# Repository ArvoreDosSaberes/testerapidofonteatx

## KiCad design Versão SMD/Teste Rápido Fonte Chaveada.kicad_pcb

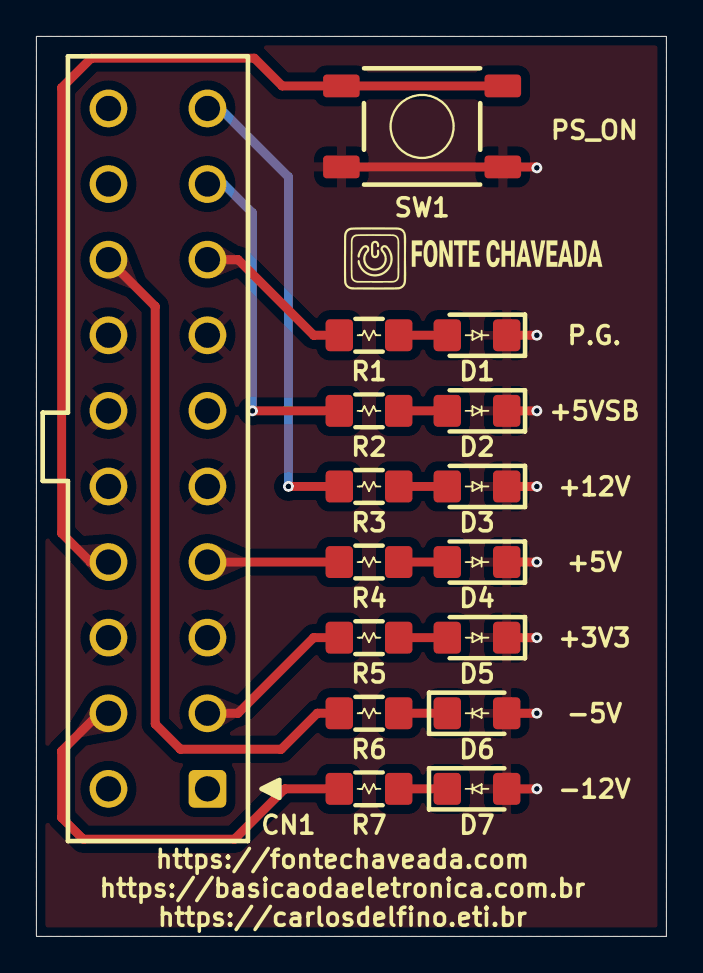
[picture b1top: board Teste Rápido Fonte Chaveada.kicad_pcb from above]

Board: 2 copper layers, 35.0 x 50.0 mm, 16 parts (0 on the bottom side), 16 nets.

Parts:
CN1: W4505-20PDRDTXR
D1, D2, D3, D4, D5, D6, D7: LED; LED_1206_HandSolder
R1, R4, R6: 470R; RES_1206_HandSolder
R2: 680R; RES_1206_HandSolder
R3: 1K8R; RES_1206_HandSolder
R5: 100R; RES_1206_HandSolder
R7: 1k8R; RES_1206_HandSolder
SW1: SW_DPST_x2; SW_Push_1P1T_NO_6x6mm_H9.5mm

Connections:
+3.3V: CN1.1, CN1.2, CN1.11, R5.1
+5V: CN1.4, CN1.6, CN1.19, CN1.20, R4.1
+5V_SB: CN1.9, R2.1
+12V: CN1.10, R3.1
+P_G: CN1.8, R1.1
-5V: CN1.18, R6.1
-12V: CN1.12, R7.1
/PS_ON: CN1.14, SW1.2 (B)
GND: CN1.3, CN1.5, CN1.7, CN1.13, CN1.15, CN1.16, CN1.17, D1.1 (K), D2.1 (K), D3.1 (K), D4.1 (K), D5.1 (K), D6.2 (A), D7.2 (A), SW1.1 (A)
unnamed: D1.2 (A), R1.2
unnamed: D2.2 (A), R2.2
unnamed: D3.2 (A), R3.2
unnamed: D4.2 (A), R4.2
unnamed: D5.2 (A), R5.2
unnamed: D6.1 (K), R6.2
unnamed: D7.1 (K), R7.2

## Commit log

2024-11-10 Primeiro Commit
2024-11-11 Atualização da placa v0.1 (@JefersonMarcante)
2024-11-12 Atualização da placa v1
2024-11-13 Arquivos a serem ignorados.
2024-11-13 Arquivos originais dos Logos
2024-11-13 Mais arquivos a serem ignorados.
2024-11-13 Adicionado cargas de teste por Rail.
